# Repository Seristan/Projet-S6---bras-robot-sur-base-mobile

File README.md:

# Repository à jour : https://github.com/Seristan/Bras-Robot-sur-base-mobile

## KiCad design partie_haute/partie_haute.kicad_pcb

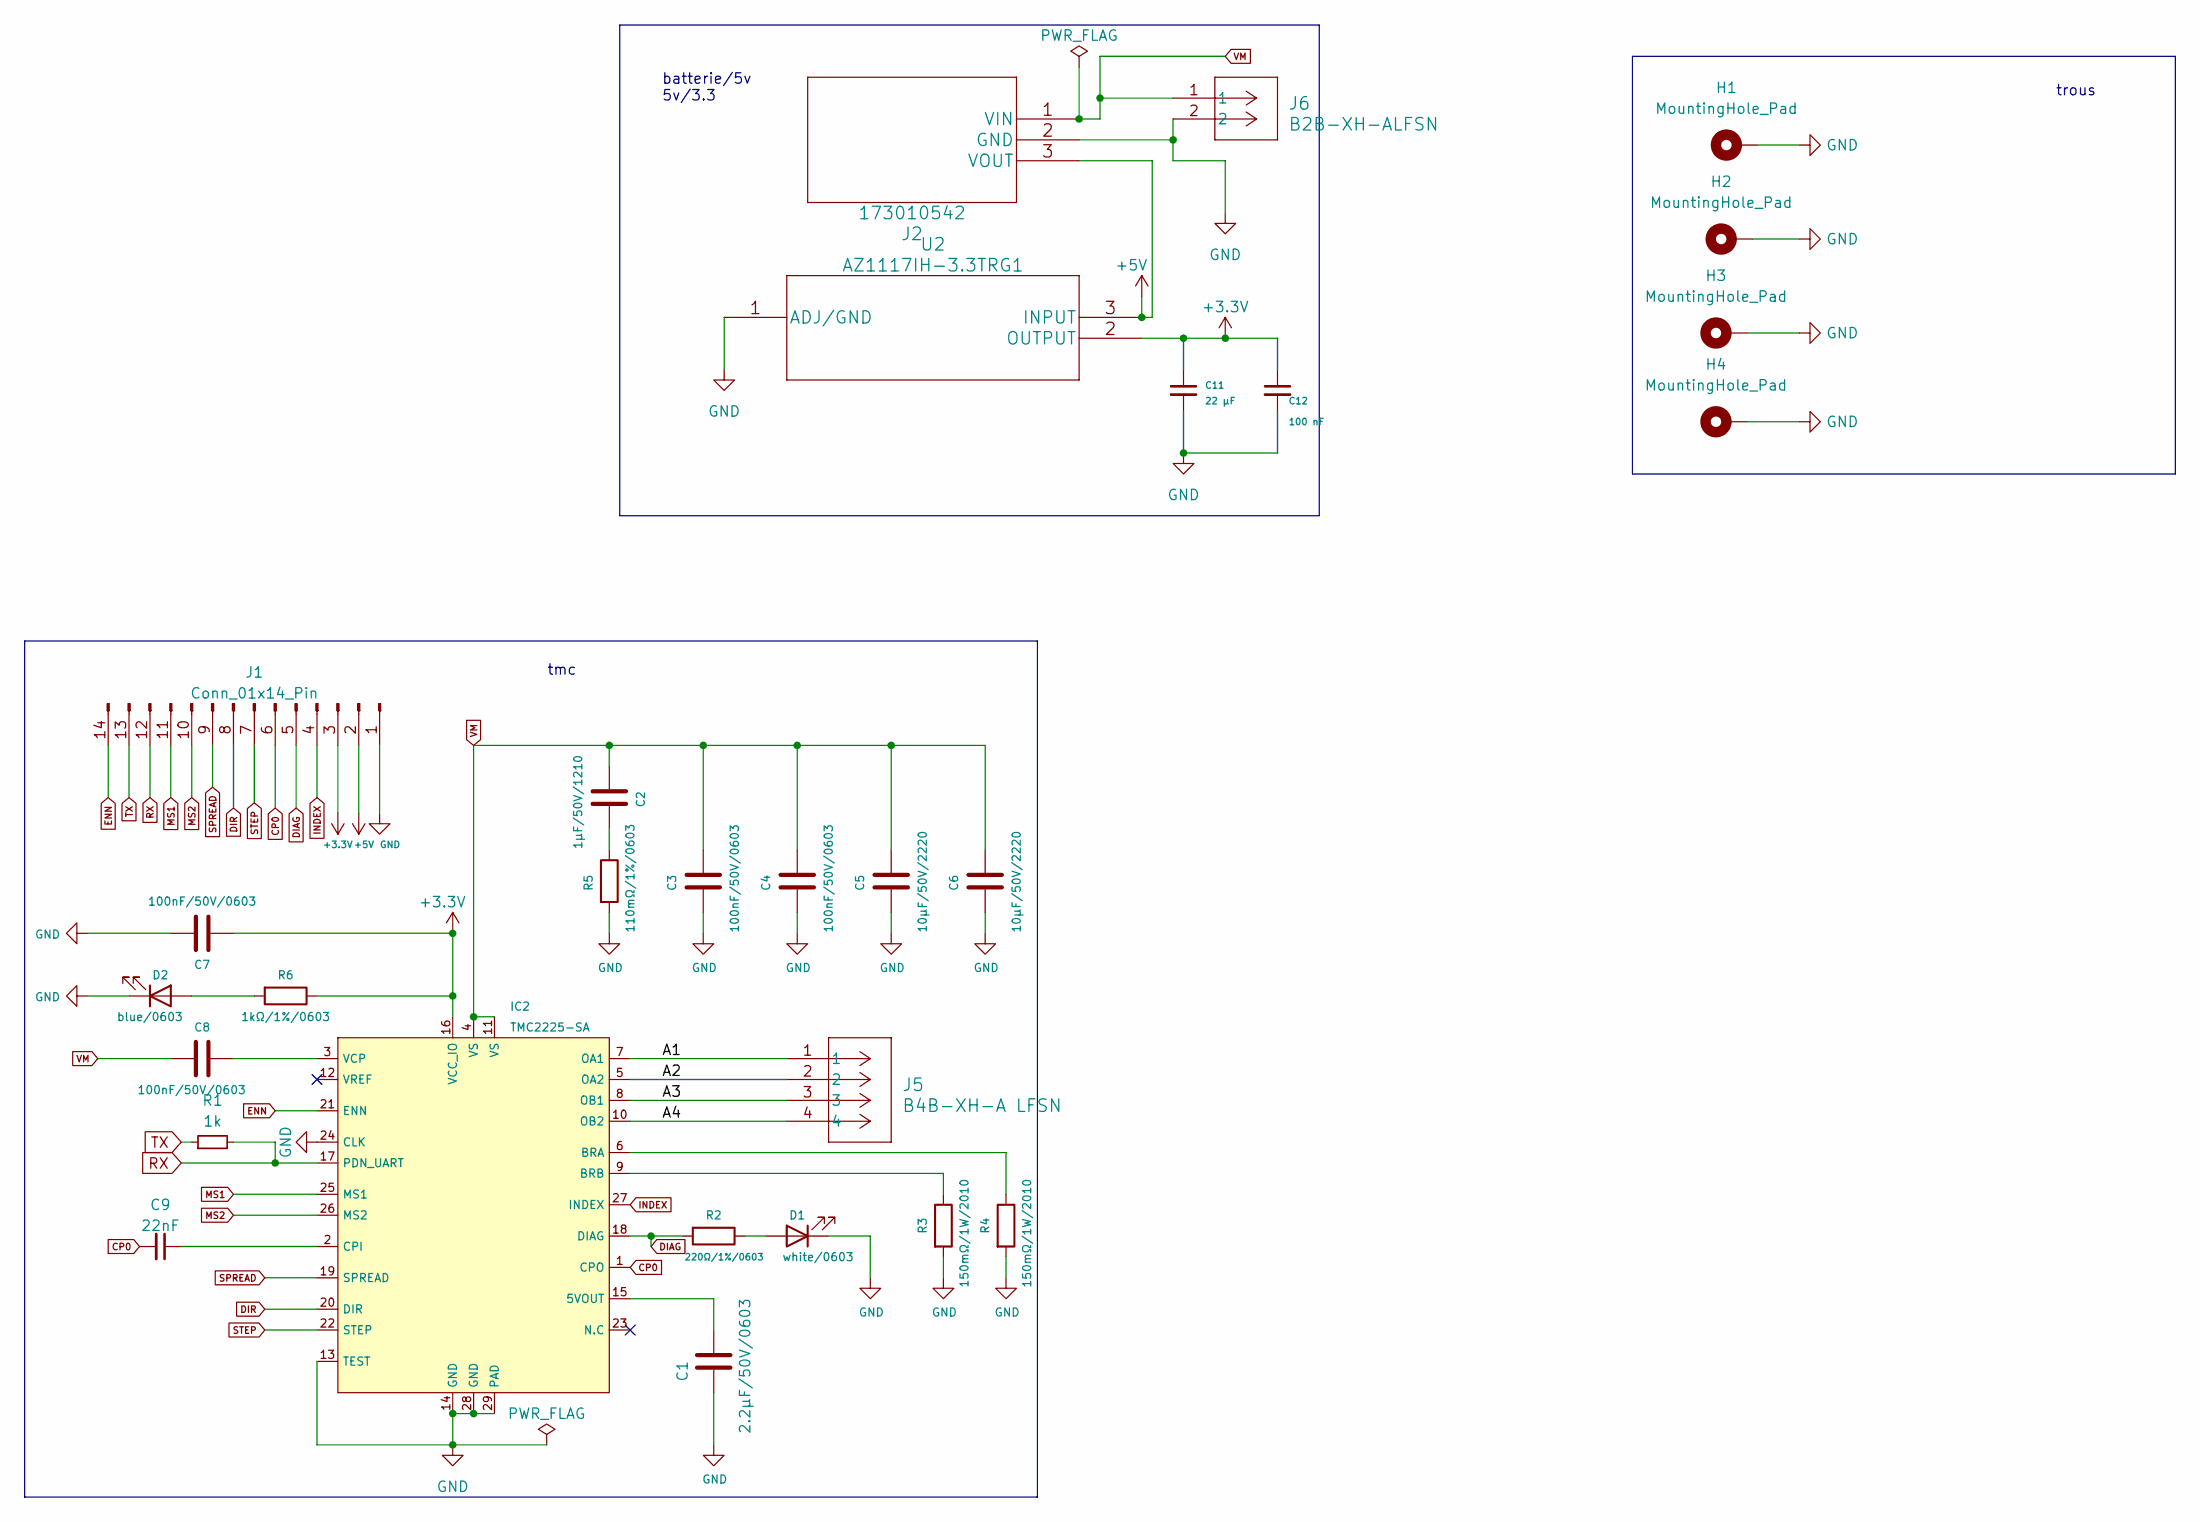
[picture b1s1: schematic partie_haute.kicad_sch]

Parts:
C1: 2.2µF/50V/0603; C_0603_1608Metric_Pad1.08x0.95mm_HandSolder
C2: 1µF/50V/1210; C_1210_3225Metric
C3, C4, C7, C8: 100nF/50V/0603; C_0603_1608Metric
C5, C6: 10µF/50V/2220; C_2220_5650Metric
C9: 22nF; C_0603_1608Metric_Pad1.08x0.95mm_HandSolder
C11: 22 µF; C_2220_5650Metric_Pad1.97x5.40mm_HandSolder
C12: 100 nF; C_0603_1608Metric_Pad1.08x0.95mm_HandSolder
D1: white/0603; LED_0603_1608Metric_Pad1.05x0.95mm_HandSolder
D2: blue/0603; LED_0603_1608Metric_Pad1.05x0.95mm_HandSolder
H1, H2, H3, H4: MountingHole_Pad; MountingHole_2.2mm_M2_DIN965_Pad
IC2: TMC2225-SA; HTSSOP28_TRI
J1: Conn_01x14_Pin; PinHeader_2x07_P2.00mm_Vertical
J2: 173010542
J5: B4B-XH-A LFSN; CONN_B4B-XH-A LFSN_JST
J6: B2B-XH-ALFSN; CONN_B2B-XH-ALFSN_JST
R1: 1k; R_0603_1608Metric_Pad0.98x0.95mm_HandSolder
R2: 220Ω/1%/0603; R_0603_1608Metric
R3, R4: 150mΩ/1W/2010; R_2010_5025Metric
R5: 110mΩ/1%/0603; R_0603_1608Metric
R6: 1kΩ/1%/0603; R_0603_1608Metric
U2: AZ1117IH-3.3TRG1

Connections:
+3.3V: C7.1, C11.1, C12.1, IC2.16 (VCC_IO), J1.3, R6.1, U2.2 (OUTPUT)
+5V: J1.2, J2.3 (VOUT), U2.3 (INPUT)
/A1: IC2.7 (OA1), J5.1
/A2: IC2.5 (OA2), J5.2
/A3: IC2.8 (OB1), J5.3
/A4: IC2.10 (OB2), J5.4
CP0: C9.2, IC2.1 (CPO), J1.6
DIAG: IC2.18 (DIAG), J1.5, R2.2
DIR: IC2.20 (DIR), J1.8
ENN: IC2.21 (ENN), J1.14
GND: C1.2, C3.2, C4.2, C5.2, C6.2, C7.2, C11.2, C12.2, D1.1 (K), D2.1 (K), H1.1, H2.1, H3.1, H4.1, IC2.13 (TEST), IC2.14 (GND), IC2.24 (CLK), IC2.28 (GND), IC2.29 (PAD), J1.1, J2.2 (GND), J6.2, R3.2, R4.2, R5.2, U2.1 (ADJ/GND)
INDEX: IC2.27 (INDEX), J1.4
MS1: IC2.25 (MS1), J1.11
MS2: IC2.26 (MS2), J1.10
unnamed: C2.2, R5.1
unnamed: D1.2 (A), R2.1
unnamed: D2.2 (A), R6.2
unnamed: C1.1, IC2.15 (5VOUT)
unnamed: IC2.6 (BRA), R4.1
unnamed: IC2.9 (BRB), R3.1
unnamed: C9.1, IC2.2 (CPI)
unnamed: C8.2, IC2.3 (VCP)
RX: IC2.17 (PDN_UART), J1.12, R1.2
SPREAD: IC2.19 (SPREAD), J1.9
STEP: IC2.22 (STEP), J1.7
TX: J1.13, R1.1
VM: C2.1, C3.1, C4.1, C5.1, C6.1, C8.1, IC2.4 (VS), IC2.11 (VS), J2.1 (VIN), J6.1

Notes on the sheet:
batterie/5v 5v/3.3
trous
tmc

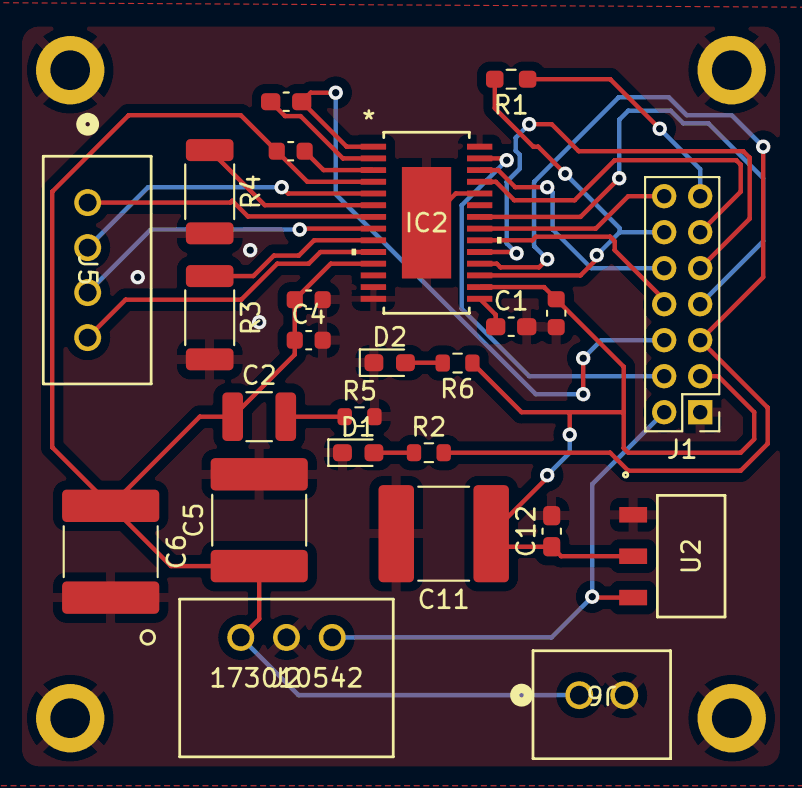
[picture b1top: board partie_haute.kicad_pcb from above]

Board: 2 copper layers, 29 parts (0 on the bottom side), 27 nets.

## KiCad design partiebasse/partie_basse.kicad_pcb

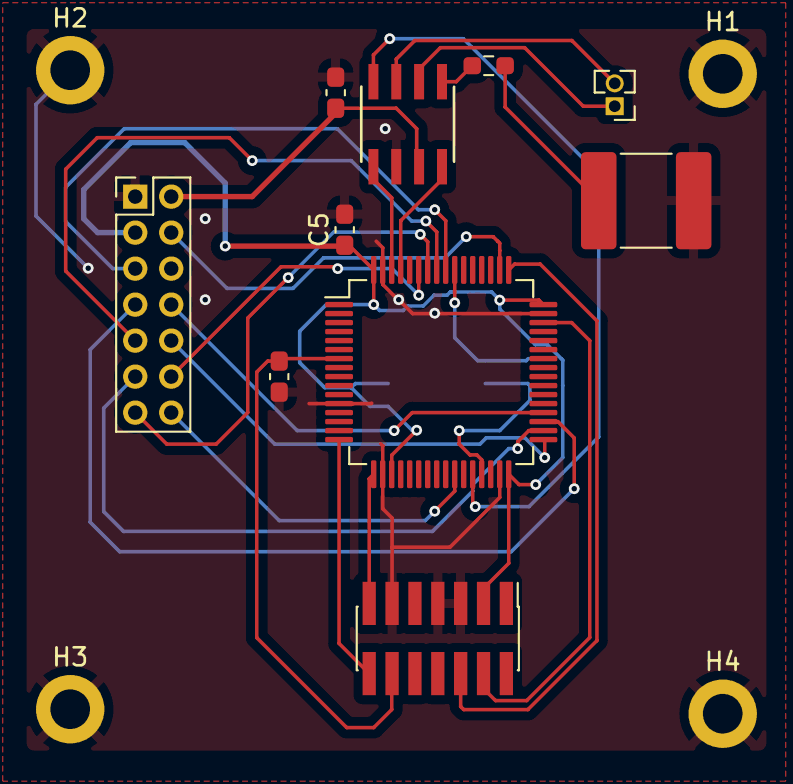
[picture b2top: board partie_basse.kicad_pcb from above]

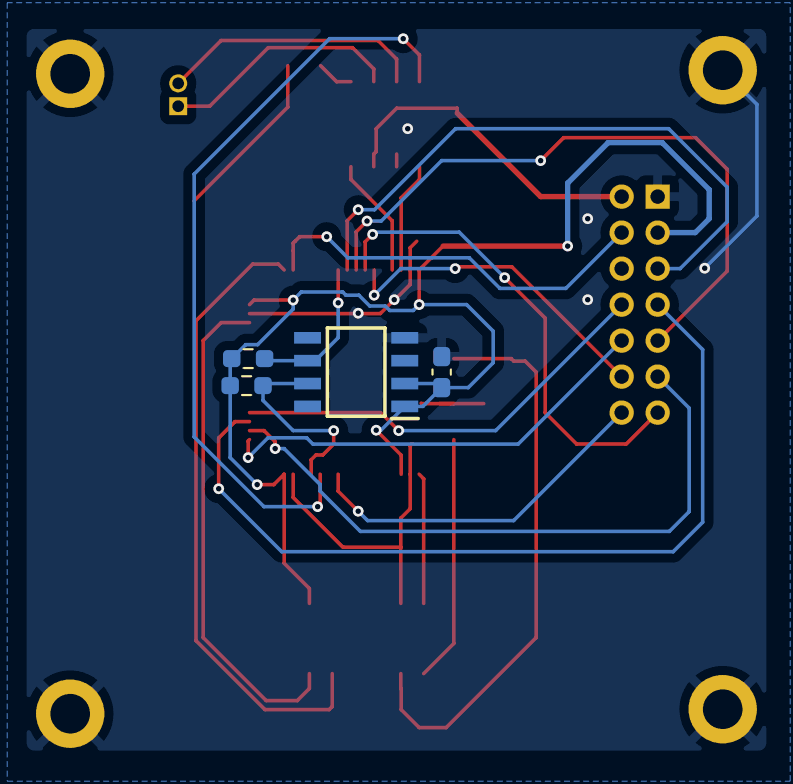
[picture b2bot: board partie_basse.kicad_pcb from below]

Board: 2 copper layers, 18 parts (4 on the bottom side), 27 nets.

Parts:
C1, C4: 100 nF; C_0603_1608Metric_Pad1.08x0.95mm_HandSolder
C2, C5: 0.1 µF; C_0603_1608Metric_Pad1.08x0.95mm_HandSolder
C3: 22 µF; C_2220_5650Metric_Pad1.97x5.40mm_HandSolder
H1, H2, H3, H4: MountingHole_Pad; MountingHole_2.2mm_M2_DIN965_Pad
IC1: AS5600-ASOT; SOIC127P600X175-8N
J1: Conn_02x07_Odd_Even; PinHeader_2x07_P1.27mm_Vertical_SMD
J2: Conn_01x02_Pin; PinHeader_1x02_P1.27mm_Vertical
J3: Conn_01x14_Pin; PinHeader_2x07_P2.00mm_Vertical
R1, R2: 1.8K; R_0603_1608Metric_Pad0.98x0.95mm_HandSolder
R3: 300; R_0603_1608Metric_Pad0.98x0.95mm_HandSolder
U1: MCP2562-E/SN; MCP2562-E&slash_SN
U2: STM32F446RETx; LQFP-64_10x10mm_P0.5mm

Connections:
+3.3V: C1.1, C5.1, IC1.1 (VDD5V), IC1.2 (VDD3V3), J1.3, J3.3, R1.1, R2.1, U2.19 (VDD), U2.32 (VDD), U2.48 (VDD), U2.64 (VDD)
+5V: C2.1, J3.2, U1.3 (VDD)
CAN_RX: U1.4 (RXD), U2.61 (PB8)
CAN_TX: U1.1 (TXD), U2.62 (PB9)
DIAG: J3.5, U2.56 (PB4)
DIR: J3.8, U2.36 (PB15)
ENN: J3.14, U2.26 (PB0)
GND: C1.2, C2.2, C3.2, C4.2, C5.2, H1.1, H2.1, H3.1, H4.1, IC1.4 (GND), J1.5, J1.7, J1.11, J3.1, U1.2 (VSS), U2.12 (VSSA), U2.18 (VSS), U2.31 (VSS), U2.47 (VSS), U2.63 (VSS)
INDEX: J3.4, U2.50 (PA15)
MS1: J3.11, U2.34 (PB13)
MS2: J3.10, U2.33 (PB12)
NRST: C4.1, J1.12, U2.7 (NRST)
unnamed: C3.1, R3.2
unnamed: J2.1, U1.6 (CANL)
unnamed: J2.2, U1.7 (CANH)
unnamed: R3.1, U1.5 (SPLIT)
RX: J3.12, U2.59 (PB7)
SCL: IC1.7 (SCL), R1.2, U2.29 (PB10)
SDA: IC1.6 (SDA), R2.2, U2.55 (PB3)
SPREAD: J3.9, U2.57 (PB5)
STBY: U1.8 (STBY), U2.28 (PB2)
STEP: J3.7, U2.35 (PB14)
SWDCK: J1.6, U2.49 (PA14)
SWDIO: J1.4, U2.46 (PA13)
TX: J3.13, U2.58 (PB6)
USART2_RX: J1.13, U2.17 (PA3)
USART2_TX: J1.14, U2.16 (PA2)

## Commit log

2023-04-18 Add files via upload
    PCB regroupant toutes les cartes
2023-05-05 Add files via upload
    Schéma complet
2023-06-05 README.md

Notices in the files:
parts and their libraries:
Copyright 2016 Accelerated Designs. All rights reserved.
